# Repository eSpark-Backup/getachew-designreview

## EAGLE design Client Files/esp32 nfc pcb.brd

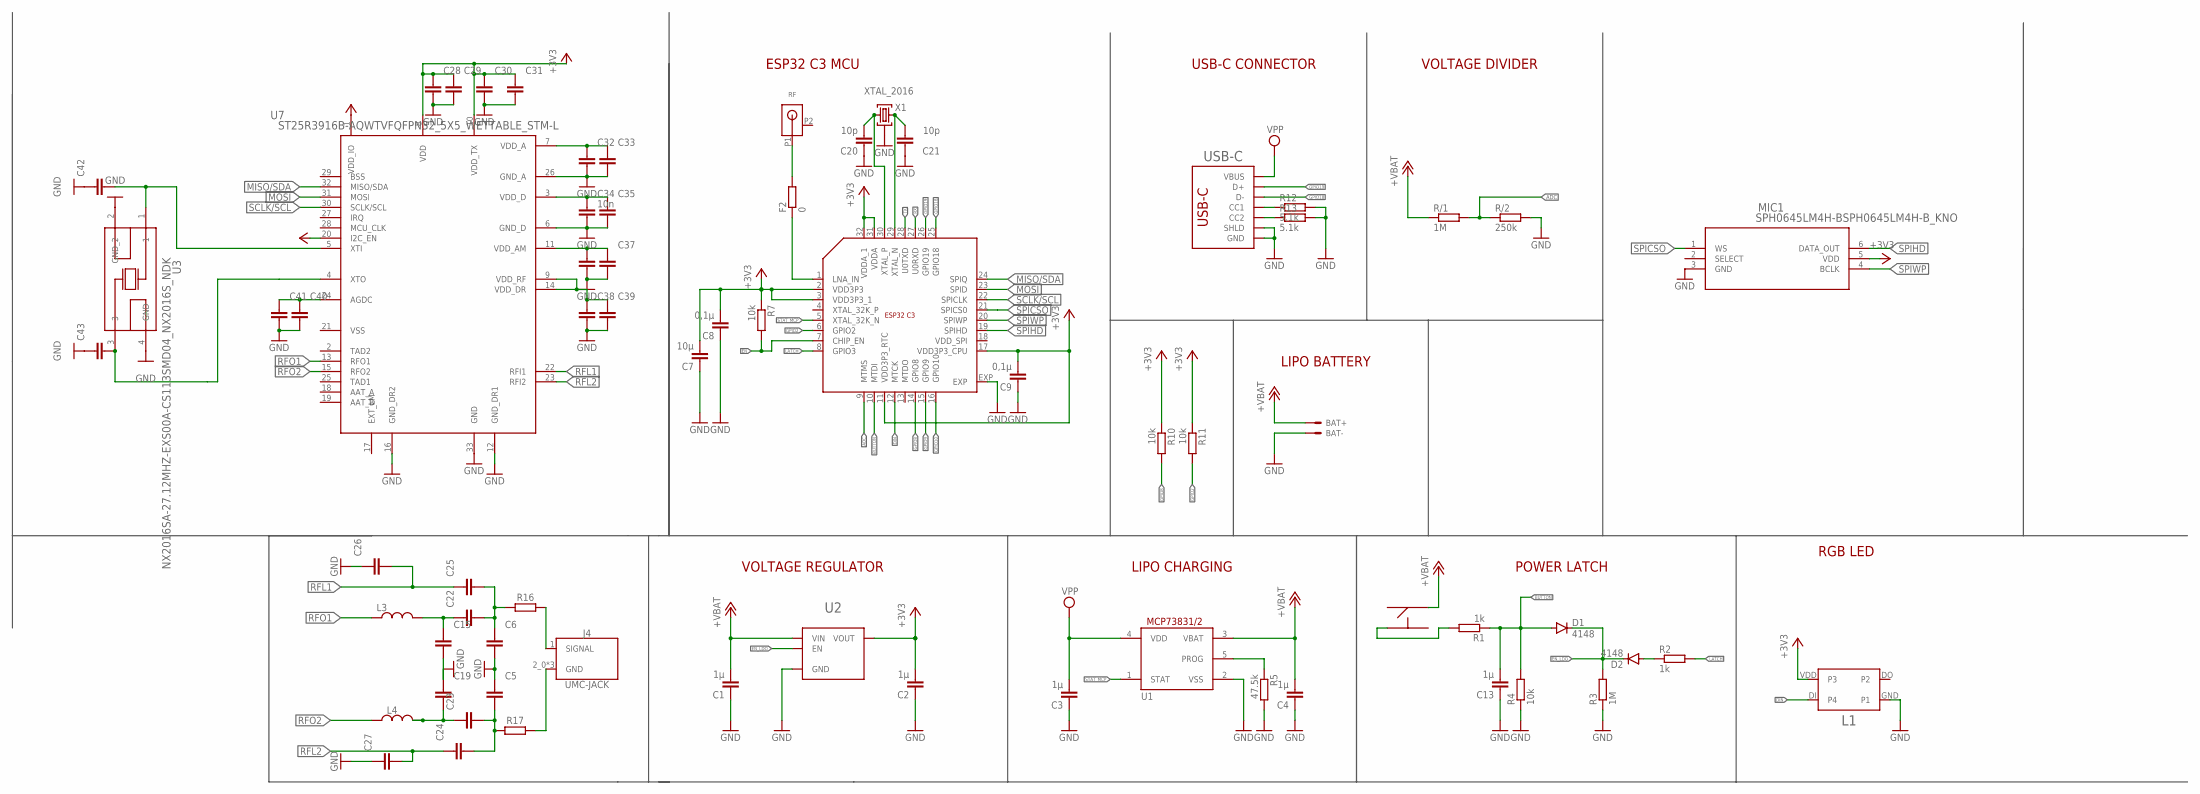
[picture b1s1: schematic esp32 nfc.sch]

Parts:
BAT+: TP/SP-1.5X1.0; SOLDERPAD_1.5X1.0
BAT-: TP/SP-1.5X1.0; SOLDERPAD_1.5X1.0
C1, C2, C3, C4, C13: 1µ; C0402_S
C5, C6, C15, C19, C22, C23, C24, C25, C26, C27, C28, C29, C30, C31, C32, C33, C35, C36, C37, C38, C39, C40, C41, C42, C43: C_CHIP-0402(1005-METRIC); CAPC1005X60
C7: 10µ; C0402_S
C8, C9: 0,1µ; C0402_S
C20, C21: 10p; C0402_S
C34: 10n; CAPC1005X60
D1, D2: 4148; SOD523
ESP1: ESP32_C3_QFN32; QFN32
F2: 0; R0402
J4: UMC-JACK; A-1JB
L1: WS2812_2020
L3, L4: L_CHIP-0402(1006-METRIC); INDC1006X60N
MIC1: SPH0645LM4H-BSPH0645LM4H-B_KNO; SPH0645LM4H-B_KNO
R1, R2: 1k; R0402
R3: 1M; R0402
R4, R7, R10, R11: 10k; R0402
R5: 47.5k; R0402
R12, R13: 5.1k; R0402
R16, R17: R_CHIP-0402(1005-METRIC); RESC1005X40
R/1: 1M; R0402
R/2: 250k; R0402
RF: ANT3216LL00R2400A
U1: BRCL4054BME; SOT23-5
U2: MIC5504; TDFN4
U3: NX2016SA-27.12MHZ-EXS00A-CS113SMD04_NX2016S_NDK; SMD04_NX2016S_NDK
U7: ST25R3916B-AQWTVFQFPN32_5X5_WETTABLE_STM-L; VFQFPN32_5X5_WETTABLE_STM-L
U$1: BUTTON_ST-1187-3
USB-C: USB_C_C393939; USBC_C393939
X1: XTAL_2016; XTYL_2016

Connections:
+3V3: C2.P$2 (2), C7.P$2 (2), C8.P$2 (2), C9.P$2 (2), C28.1, C29.1, C30.1, C31.1, ESP1.2 (VDD3P3), ESP1.3 (VDD3P3_1), ESP1.11 (VDD3P3_RTC), ESP1.17 (VDD3P3_CPU), ESP1.31 (VDDA), ESP1.32 (VDDA_1), L1.VDD (P3), MIC1.5 (VDD), R7.1, R10.1, R11.1, U2.P1 (VOUT), U7.1 (VDD_IO), U7.8 (VDD), U7.10 (VDD_TX), U7.20 (I2C_EN)
+VBAT: BAT+.1, C1.P$2 (2), C4.P$2 (2), R/1.1, U1.3 (VBAT), U2.P4 (VIN), U$1.P2
ADC: ESP1.9 (MTMS), R/1.2, R/2.1
BUTTON: C13.P$2 (2), D1.A, ESP1.10 (MTDI), R1.1, R4.2
DIN: ESP1.12 (MTCK), L1.DI (P4)
EN: ESP1.7 (CHIP_EN), R7.2
EN_LDO: D1.C, D2.C, R3.2, U2.P3 (EN)
GND: BAT-.1, C1.P$1 (1), C2.P$1 (1), C3.P$1 (1), C4.P$1 (1), C5.1, C6.2, C7.P$1 (1), C8.P$1 (1), C9.P$1 (1), C13.P$1 (1), C15.2, C19.1, C20.P$1 (1), C21.P$1 (1), C26.1, C27.1, C28.2, C29.2, C30.2, C31.2, C32.2, C33.2, C34.2, C35.2, C36.2, C37.2, C38.2, C39.2, C40.2, C41.2, C42.1, C43.1, ESP1.EXP, L1.GND (P1), MIC1.3 (GND), R3.1, R4.1, R5.2, R12.2, R13.2, R/2.2, U1.2 (VSS), U2.EXP (GND), U2.P2 (GND), U3.2 (GND_2), U3.4 (GND), U7.6 (GND_D), U7.12 (GND_DR1), U7.16 (GND_DR2), U7.26 (GND_A), U7.33 (GND), USB-C.A1B12 (GND), USB-C.B1A12 (GND), USB-C.S1 (SHLD), USB-C.S2 (SHLD), USB-C.S3 (SHLD), USB-C.S4 (SHLD), X1.P2 (G), X1.P4 (G)
GPIO2: ESP1.6 (GPIO2), R11.2
GPIO8: ESP1.14 (GPIO8), R10.2
GPIO9: ESP1.15 (GPIO9)
GPIO10: ESP1.16 (GPIO10)
GPIO18: ESP1.25 (GPIO18), USB-C.A7 (D-), USB-C.B7 (D-)
GPIO19: ESP1.26 (GPIO19), USB-C.A6 (D+), USB-C.B6 (D+)
LATCH: ESP1.8 (GPIO3), R2.2
MISO/SDA: ESP1.22 (SPICLK), U7.32 (MISO/SDA)
MOSI: ESP1.23 (SPID), U7.31 (MOSI)
unnamed: R1.2, U$1.P3
unnamed: C19.2, C23.1, L4.2
unnamed: C42.2, U3.1, U7.5 (XTI)
unnamed: ESP1.1 (LNA_IN), F2.1
unnamed: C15.1, C22.1, L3.2
unnamed: F2.2, RF.P1 (ANT)
unnamed: C32.1, C33.1, U7.7 (VDD_A)
unnamed: C5.2, C23.2, C24.2, R17.1
unnamed: C6.1, C22.2, C25.2, R16.1
unnamed: D2.A, R2.1
unnamed: R13.1, USB-C.B5 (CC2)
unnamed: R5.1, U1.5 (PROG)
unnamed: R12.1, USB-C.A5 (CC1)
unnamed: C20.P$2 (2), ESP1.30 (XTAL_P), X1.P1 (1)
unnamed: C21.P$2 (2), ESP1.29 (XTAL_N), X1.P3 (2)
unnamed: C34.1, C35.1, U7.3 (VDD_D)
unnamed: C36.1, C37.1, U7.11 (VDD_AM)
unnamed: J4.1 (SIGNAL), R16.2
unnamed: C38.1, C39.1, U7.9 (VDD_RF), U7.14 (VDD_DR)
unnamed: C43.2, U3.3, U7.4 (XTO)
unnamed: J4.2_0 (GND), J4.2_1 (GND), J4.2_2 (GND), R17.2
unnamed: C40.1, C41.1, U7.24 (AGDC)
RFL1: C25.1, C26.2, U7.22 (RFI1)
RFL2: C24.1, C27.2, U7.23 (RFI2)
RFO1: L3.1, U7.13 (RFO1)
RFO2: L4.1, U7.15 (RFO2)
RX: ESP1.27 (U0RXD)
SCLK/SCL: ESP1.24 (SPIQ), U7.30 (SCLK/SCL)
SPICSO: ESP1.21 (SPICS0), MIC1.1 (WS)
SPIHD: ESP1.19 (SPIHD), MIC1.6 (DATA_OUT)
SPIWP: ESP1.20 (SPIWP), MIC1.4 (BCLK)
STAT_MCP: ESP1.5 (XTAL_32K_N), U1.1 (STAT)
TX: ESP1.28 (U0TXD)
VPP: C3.P$2 (2), U1.4 (VDD), USB-C.A4B9 (VBUS), USB-C.B4A9 (VBUS)

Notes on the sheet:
VOLTAGE DIVIDER
LIPO CHARGING
VOLTAGE REGULATOR
POWER LATCH
RGB LED
USB-C CONNECTOR
ESP32 C3 MCU
LIPO BATTERY

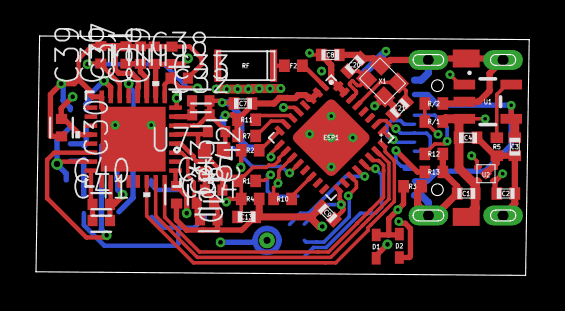
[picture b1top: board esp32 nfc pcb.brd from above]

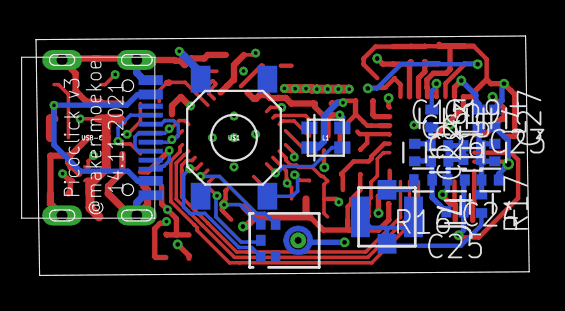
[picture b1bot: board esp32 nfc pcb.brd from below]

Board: 4 copper layers, 27.4 x 13.2 mm, 69 parts (19 on the bottom side), 47 nets.

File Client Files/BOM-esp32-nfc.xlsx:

Part | Value | Device | Package | Description | CATEGORY | COPYRIGHT | CURRENT_RATING | DESCRIPTION | MANUFACTURER | MANUFACTURER_PART_NUMBER | MFR_NAME | MPN | OPERATING_TEMP | OPERATING_TEMPERATURE | PART_STATUS | PITCH | POPULARITY | RATING | ROHS_COMPLIANCE | ROHS_COMPLIANT | SERIES | SUB-CATEGORY | SUBCATEGORY | THERMALLOSS | TOLERANCE | TYPE | VALUE | VOLTAGE_RATING
BAT+ | TP/SP-1.5X1.0 | TP/SP-1.5X1.0 | SOLDERPAD_1.5X1.0 | Solderpads/Testpads
BAT- | TP/SP-1.5X1.0 | TP/SP-1.5X1.0 | SOLDERPAD_1.5X1.0 | Solderpads/Testpads
C1 | 1µ | C-EU-0402-WOKEEPOUT_S | C0402_S
C2 | 1µ | C-EU-0402-WOKEEPOUT_S | C0402_S
C3 | 1µ | C-EU-0402-WOKEEPOUT_S | C0402_S
C4 | 1µ | C-EU-0402-WOKEEPOUT_S | C0402_S
C5 |  | C_CHIP-0402(1005-METRIC) | CAPC1005X60 | Capacitor - Generic | Capacitor
C6 |  | C_CHIP-0402(1005-METRIC) | CAPC1005X60 | Capacitor - Generic | Capacitor
C7 | 10µ | C-EU-0402-WOKEEPOUT_S | C0402_S
C8 | 0,1µ | C-EU-0402-WOKEEPOUT_S | C0402_S
C9 | 0,1µ | C-EU-0402-WOKEEPOUT_S | C0402_S
C13 | 1µ | C-EU-0402-WOKEEPOUT_S | C0402_S
C15 |  | C_CHIP-0402(1005-METRIC) | CAPC1005X60 | Capacitor - Generic | Capacitor
C19 |  | C_CHIP-0402(1005-METRIC) | CAPC1005X60 | Capacitor - Generic | Capacitor
C20 | 10p | C-EU-0402-WOKEEPOUT_S | C0402_S
C21 | 10p | C-EU-0402-WOKEEPOUT_S | C0402_S
C22 |  | C_CHIP-0402(1005-METRIC) | CAPC1005X60 | Capacitor - Generic | Capacitor
C23 |  | C_CHIP-0402(1005-METRIC) | CAPC1005X60 | Capacitor - Generic | Capacitor
C24 |  | C_CHIP-0402(1005-METRIC) | CAPC1005X60 | Capacitor - Generic | Capacitor
C25 |  | C_CHIP-0402(1005-METRIC) | CAPC1005X60 | Capacitor - Generic | Capacitor
C26 |  | C_CHIP-0402(1005-METRIC) | CAPC1005X60 | Capacitor - Generic | Capacitor
C27 |  | C_CHIP-0402(1005-METRIC) | CAPC1005X60 | Capacitor - Generic | Capacitor
C28 |  | C_CHIP-0402(1005-METRIC) | CAPC1005X60 | Capacitor - Generic | Capacitor
C29 |  | C_CHIP-0402(1005-METRIC) | CAPC1005X60 | Capacitor - Generic | Capacitor
C30 |  | C_CHIP-0402(1005-METRIC) | CAPC1005X60 | Capacitor - Generic | Capacitor
C31 |  | C_CHIP-0402(1005-METRIC) | CAPC1005X60 | Capacitor - Generic | Capacitor
C32 |  | C_CHIP-0402(1005-METRIC) | CAPC1005X60 | Capacitor - Generic | Capacitor
C33 |  | C_CHIP-0402(1005-METRIC) | CAPC1005X60 | Capacitor - Generic | Capacitor
C34 | 10n | C_CHIP-0402(1005-METRIC) | CAPC1005X60 | Capacitor - Generic | Capacitor
C35 |  | C_CHIP-0402(1005-METRIC) | CAPC1005X60 | Capacitor - Generic | Capacitor
C36 |  | C_CHIP-0402(1005-METRIC) | CAPC1005X60 | Capacitor - Generic | Capacitor
C37 |  | C_CHIP-0402(1005-METRIC) | CAPC1005X60 | Capacitor - Generic | Capacitor
C38 |  | C_CHIP-0402(1005-METRIC) | CAPC1005X60 | Capacitor - Generic | Capacitor
C39 |  | C_CHIP-0402(1005-METRIC) | CAPC1005X60 | Capacitor - Generic | Capacitor
C40 |  | C_CHIP-0402(1005-METRIC) | CAPC1005X60 | Capacitor - Generic | Capacitor
C41 |  | C_CHIP-0402(1005-METRIC) | CAPC1005X60 | Capacitor - Generic | Capacitor
C42 |  | C_CHIP-0402(1005-METRIC) | CAPC1005X60 | Capacitor - Generic | Capacitor
C43 |  | C_CHIP-0402(1005-METRIC) | CAPC1005X60 | Capacitor - Generic | Capacitor
D1 | 4148 | DIODE-SOD523 | SOD523 | DIODE |  |  |  |  |  |  |  |  |  |  |  |  | 3
D2 | 4148 | DIODE-SOD523 | SOD523 | DIODE |  |  |  |  |  |  |  |  |  |  |  |  | 3
ESP1 | ESP32_C3_QFN32 | ESP32_C3_QFN32 | QFN32
F2 | 0 | R-EU-0402-WOKEEPOUT | R0402
J4 | UMC-JACK | A-1JB | A-1JB | U.FL (UMCC), AMC Connector Jack, Male Pin 50Ohm Surface Mount Solder | RF Connectors / Coaxial Connectors |  |  | RF Connectors / Coaxial Connectors AMC PCB JACK S/M T&R U.FL Compatible | Amphenol RF |  |  | A-1JB |  | 40°C TO +90°C | Active | - |  |  | RoHS3 Compliant |  | AMC |  | RF Connectors / Coaxial Connectors |  |  | Jack, Male Pin, Surface Mount | UMC-JACK
L1 | WS2812_2020 | WS2812_2020 | WS2812_2020
L3 |  | L_CHIP-0402(1006-METRIC) | INDC1006X60N | Inductor Fixed - Generic | Inductor |  |  |  |  |  |  |  |  |  |  |  |  |  |  |  |  | Fixed
L4 |  | L_CHIP-0402(1006-METRIC) | INDC1006X60N | Inductor Fixed - Generic | Inductor |  |  |  |  |  |  |  |  |  |  |  |  |  |  |  |  | Fixed
MIC1 | SPH0645LM4H-BSPH0645LM4H-B_KNO | SPH0645LM4H-BSPH0645LM4H-B_KNO | SPH0645LM4H-B_KNO |  |  | Copyright (C) 2024 Ultra Librarian. All rights reserved. |  |  |  | SPH0645LM4H-B | Knowles
R/1 | 1M | R-EU-0402-WOKEEPOUT | R0402
R/2 | 250k | R-EU-0402-WOKEEPOUT | R0402
R1 | 1k | R-EU-0402-WOKEEPOUT | R0402
R2 | 1k | R-EU-0402-WOKEEPOUT | R0402
R3 | 1M | R-EU-0402-WOKEEPOUT | R0402
R4 | 10k | R-EU-0402-WOKEEPOUT | R0402
R5 | 47.5k | R-EU-0402-WOKEEPOUT | R0402
R7 | 10k | R-EU-0402-WOKEEPOUT | R0402
R10 | 10k | R-EU-0402-WOKEEPOUT | R0402
R11 | 10k | R-EU-0402-WOKEEPOUT | R0402
R12 | 5.1k | R-EU-0402-WOKEEPOUT | R0402
R13 | 5.1k | R-EU-0402-WOKEEPOUT | R0402
R16 |  | R_CHIP-0402(1005-METRIC) | RESC1005X40 | Resistor Fixed - Generic | Resistor |  |  |  |  |  |  |  |  |  |  |  |  |  |  |  |  | Fixed
R17 |  | R_CHIP-0402(1005-METRIC) | RESC1005X40 | Resistor Fixed - Generic | Resistor |  |  |  |  |  |  |  |  |  |  |  |  |  |  |  |  | Fixed
RF | ANT3216LL00R2400A | ANT3216LL00R2400A | ANT3216LL00R2400A
U$1 | BUTTON_ST-1187-3 | BUTTON_ST-1187-3 | BUTTON_ST-1187-3
U1 | BRCL4054BME | MCP73831_SOT23_5 | SOT23-5
U2 | MIC5504 | MIC5504 | TDFN4
U3 | NX2016SA-27.12MHZ-EXS00A-CS113SMD04_NX2016S_NDK | NX2016SA-27.12MHZ-EXS00A-CS113SMD04_NX2016S_NDK | SMD04_NX2016S_NDK |  |  | Copyright (C) 2024 Ultra Librarian. All rights reserved. |  |  |  | NX2016SA-27.12MHZ-EXS00A-CS11337 | NDK
U7 | ST25R3916B-AQWTVFQFPN32_5X5_WETTABLE_STM-L | ST25R3916B-AQWTVFQFPN32_5X5_WETTABLE_STM-L | VFQFPN32_5X5_WETTABLE_STM-L |  |  | Copyright (C) 2024 Ultra Librarian. All rights reserved. |  |  |  | ST25R3916B-AQWT | STMicroelectronics |  |  |  |  |  |  |  |  |  |  |  |  |  |  | RFID, RF Access, Monitoring ICs
USB-C | USB_C_C393939 | USB_C_C393939 | USBC_C393939
X1 | XTAL_2016 | XTAL_2016 | XTYL_2016

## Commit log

2024-08-23 #1 Client Files and Review Report added.
2024-08-23 Folder Structure corrected.
2024-08-23 #1 Images added.

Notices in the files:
parts and their libraries:
COPYRIGHT: Copyright (C) 2024 Ultra Librarian. All rights reserved.
